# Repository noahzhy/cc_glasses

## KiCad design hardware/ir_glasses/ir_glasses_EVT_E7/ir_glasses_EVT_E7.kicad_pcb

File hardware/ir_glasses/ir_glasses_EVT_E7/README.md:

# EVT E7

**状态：静态设计验收通过，首板验证待完成。** ERC、PCB DRC 均为 0 错误、0 警告；未连接及原理图与 PCB 一致性问题均为 0。尚未进行首板实测和板厂 DFM，不能据此宣布量产放行。

唯一编辑入口：`ir_glasses_EVT_E7.kicad_pro`。

- 一张 A1 原理图：`ir_glasses_EVT_E7.kicad_sch` / `schematic.pdf`。
- 一个 PCB：`ir_glasses_EVT_E7.kicad_pcb`，已包含 carrier，无独立裸板或 carrier 工程。
- 四层、1.6 mm，所有电气元器件统一正面；光学位置、接口和机械外形沿用 E6。
- 所有过孔孔径至少 0.20 mm、外径至少 0.40 mm，单边环宽至少 0.10 mm。
- 复核及精简：`review/report.md`；验收状态：`review/validation.json`。
- 分层及装配预览：`review/pcb_layers.pdf`；采购清单：`BOM.csv`；正面贴装坐标：`assembly_positions.csv`。
- 本目录不发布制造包。E6 历史制造文件不适用于 E7。

`tools/` 为此次整改的重建和检查脚本；日常直接编辑 KiCad 工程。重建脚本会覆盖设计，不能在人工修改后直接重跑。Python 工具不引入继承类；需要 KiCad 10 的 pcbnew Python，以及 Python 3 的 sexpdata、numpy、scipy、shapely、pymupdf。

固件接口和采集协议保持 F302 版本兼容，编号 E7 不意味着更改串口协议。有效采集前等待模拟偏置稳定，首板按 `first_board_tests.csv` 验证。

量产前复核见 `review/preproduction/report.md`。工程根目录 `BOM.csv` 为逐位号明细，`BOM_采购汇总.csv` 为 39 种料号的中文采购汇总，均包含简要参数及立创商城编码；单板共 153 个装配器件。实时库存、贴片库可用性及实物验证待确认。

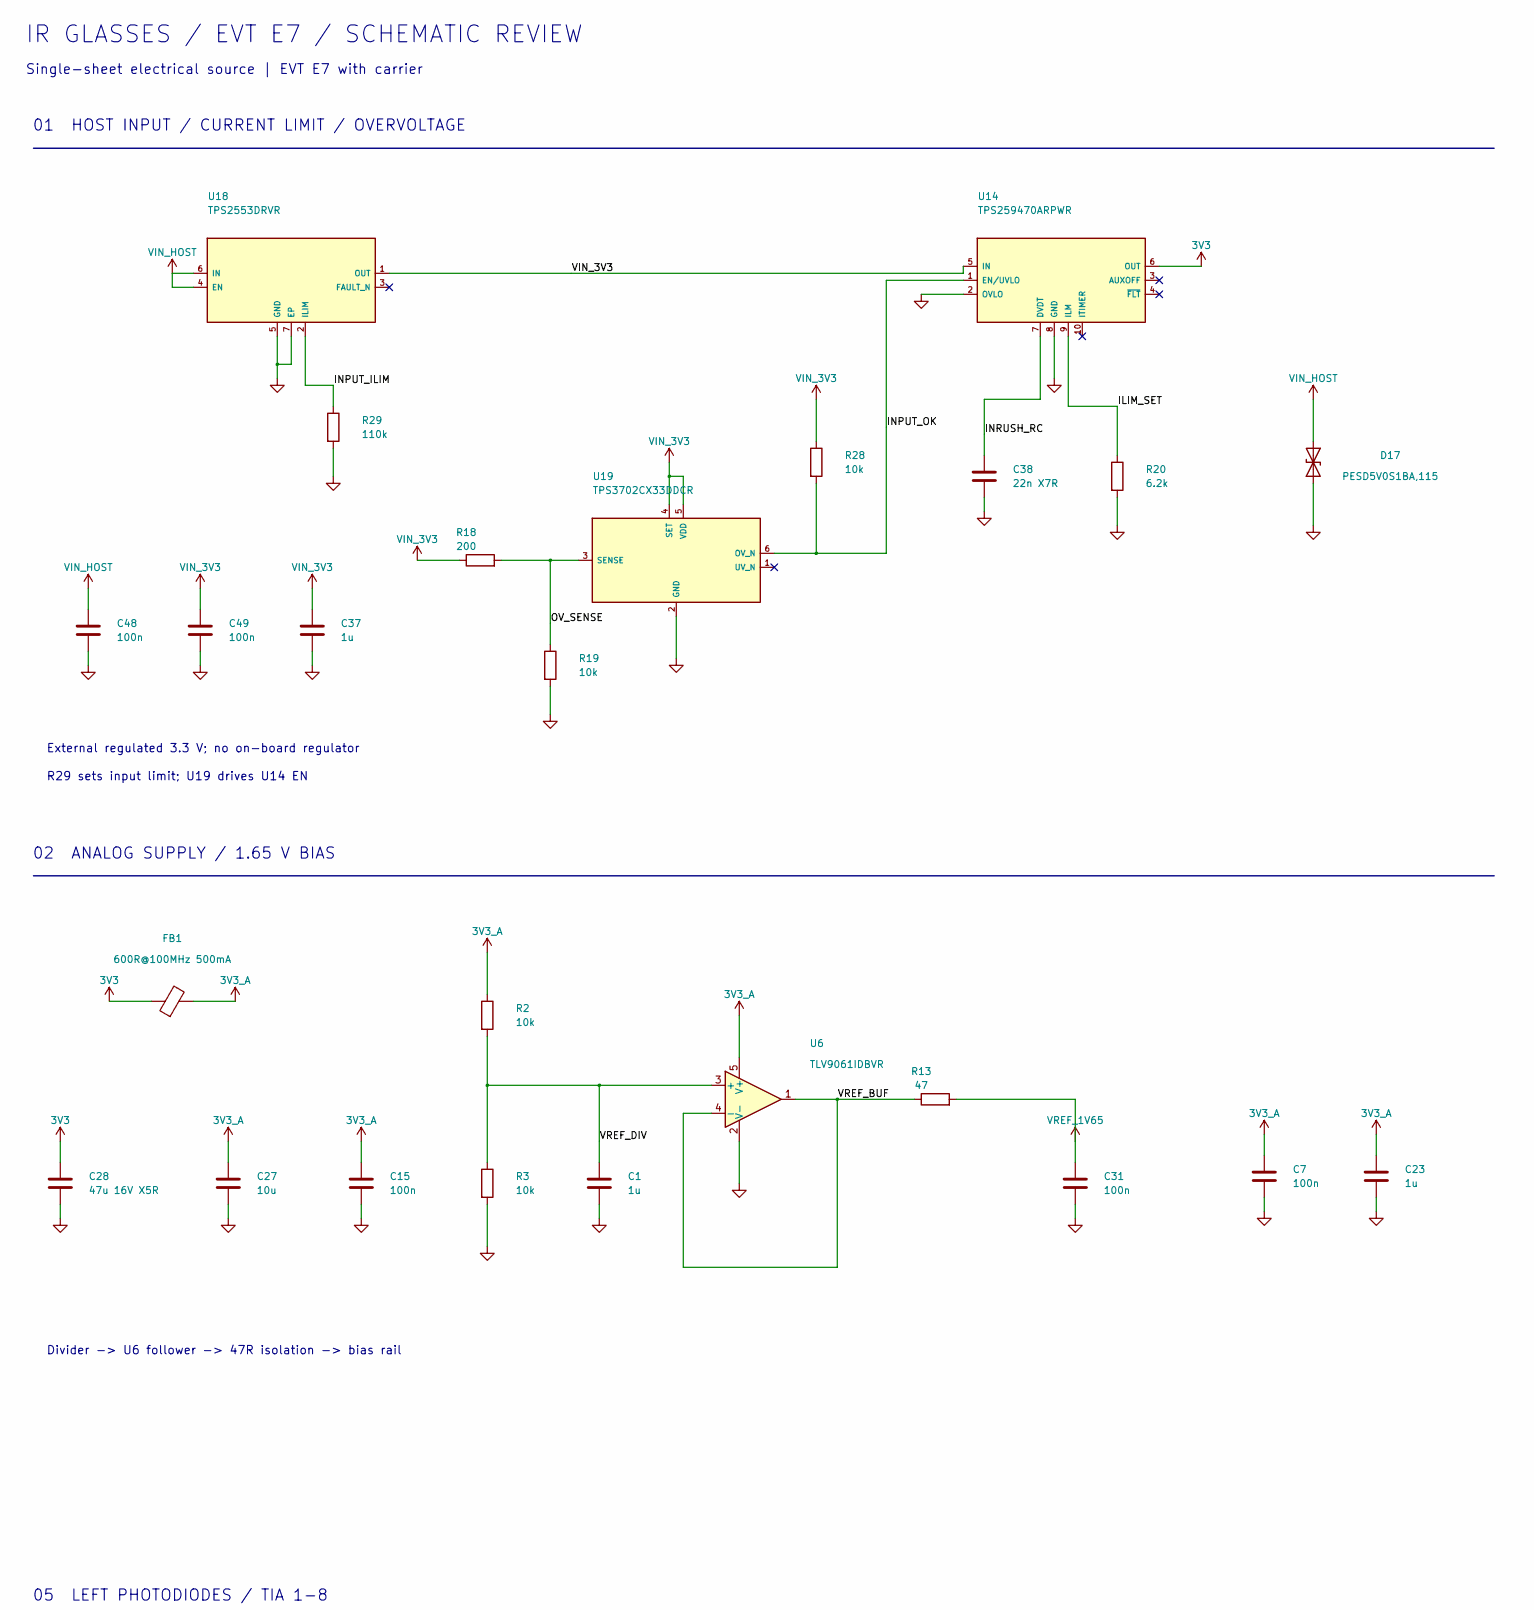
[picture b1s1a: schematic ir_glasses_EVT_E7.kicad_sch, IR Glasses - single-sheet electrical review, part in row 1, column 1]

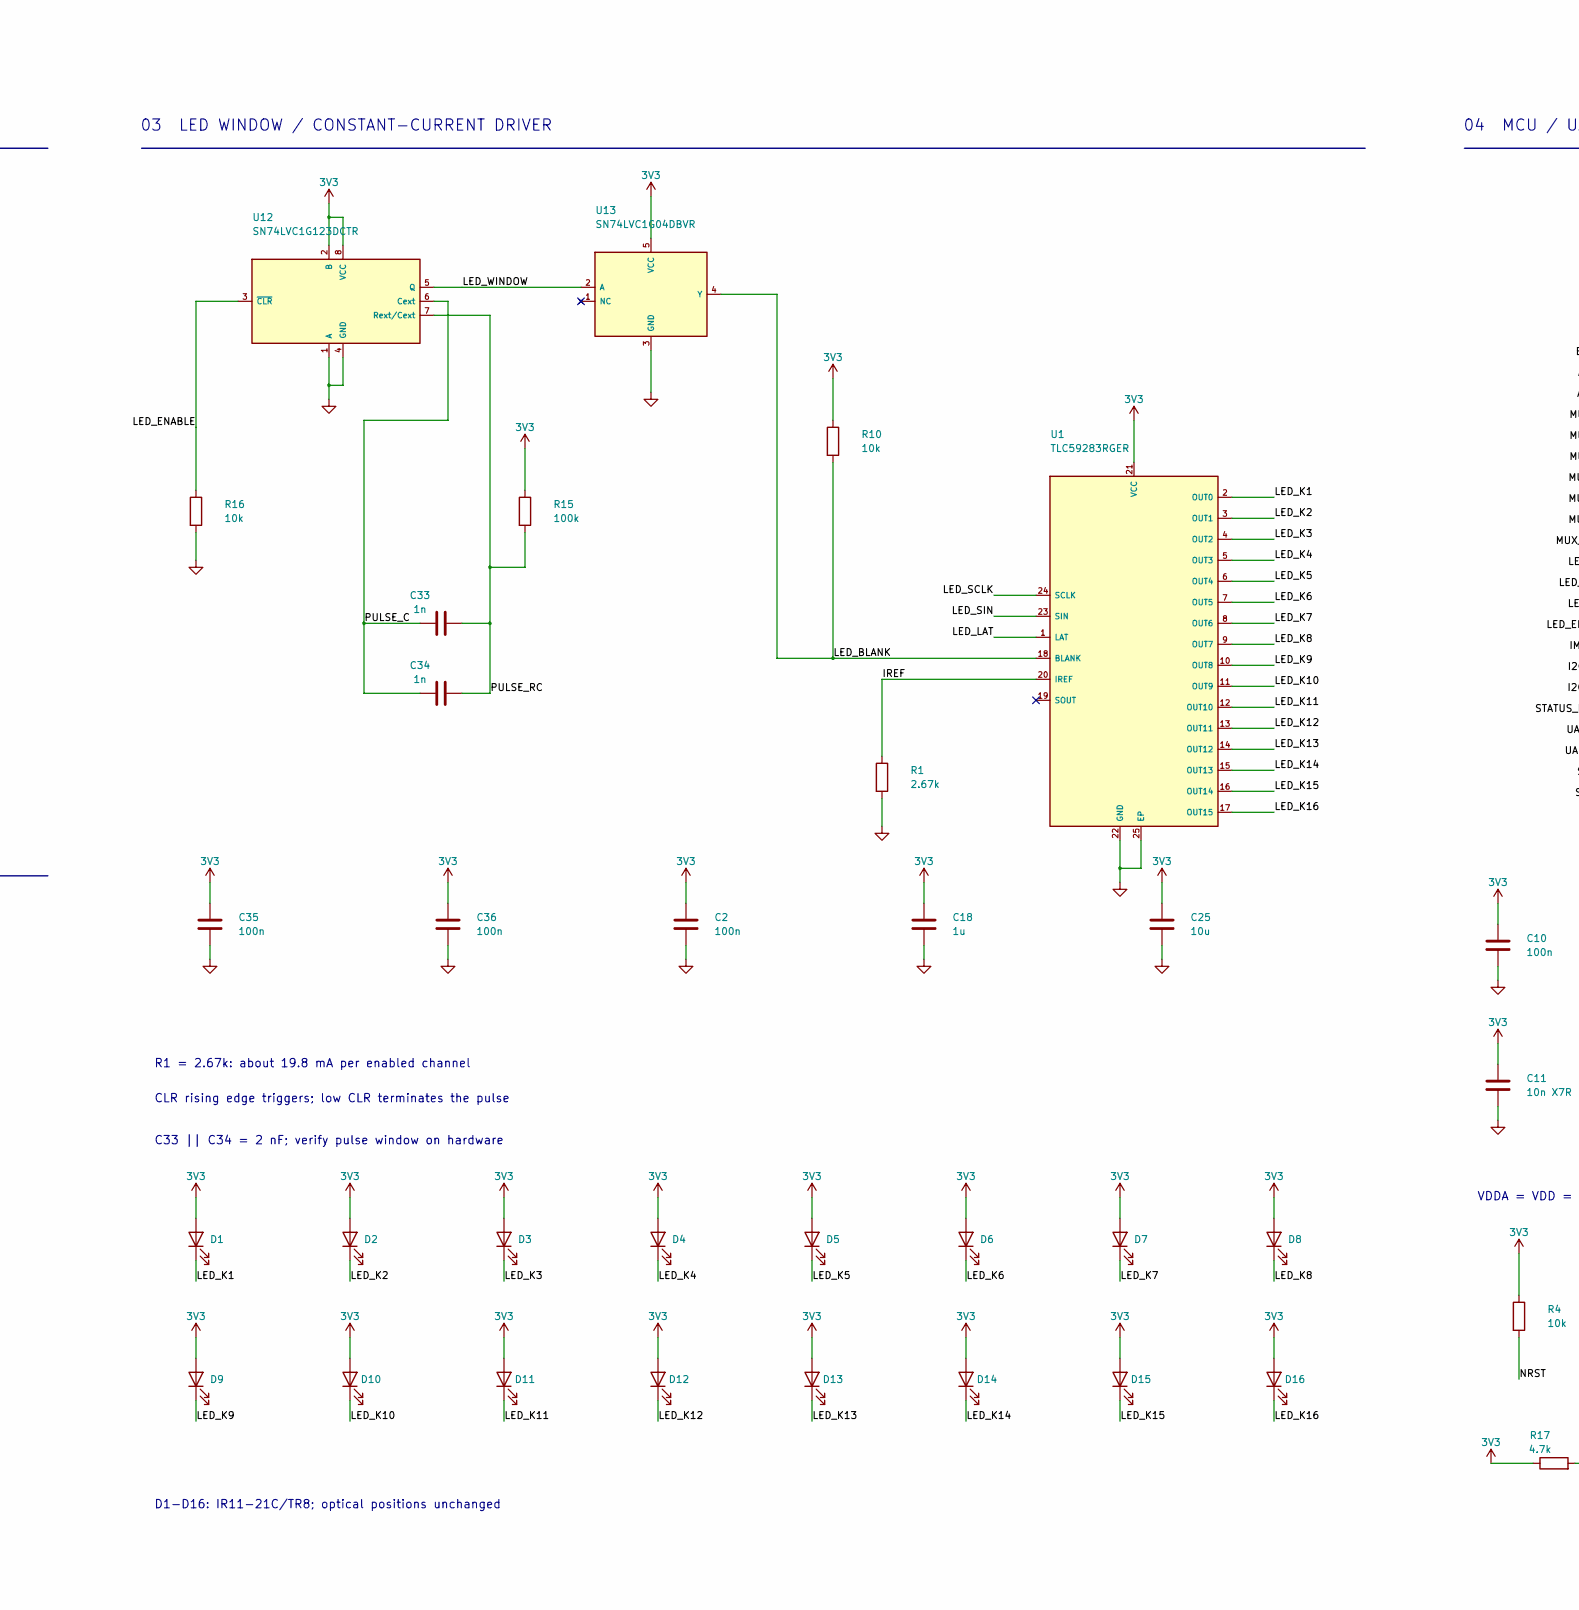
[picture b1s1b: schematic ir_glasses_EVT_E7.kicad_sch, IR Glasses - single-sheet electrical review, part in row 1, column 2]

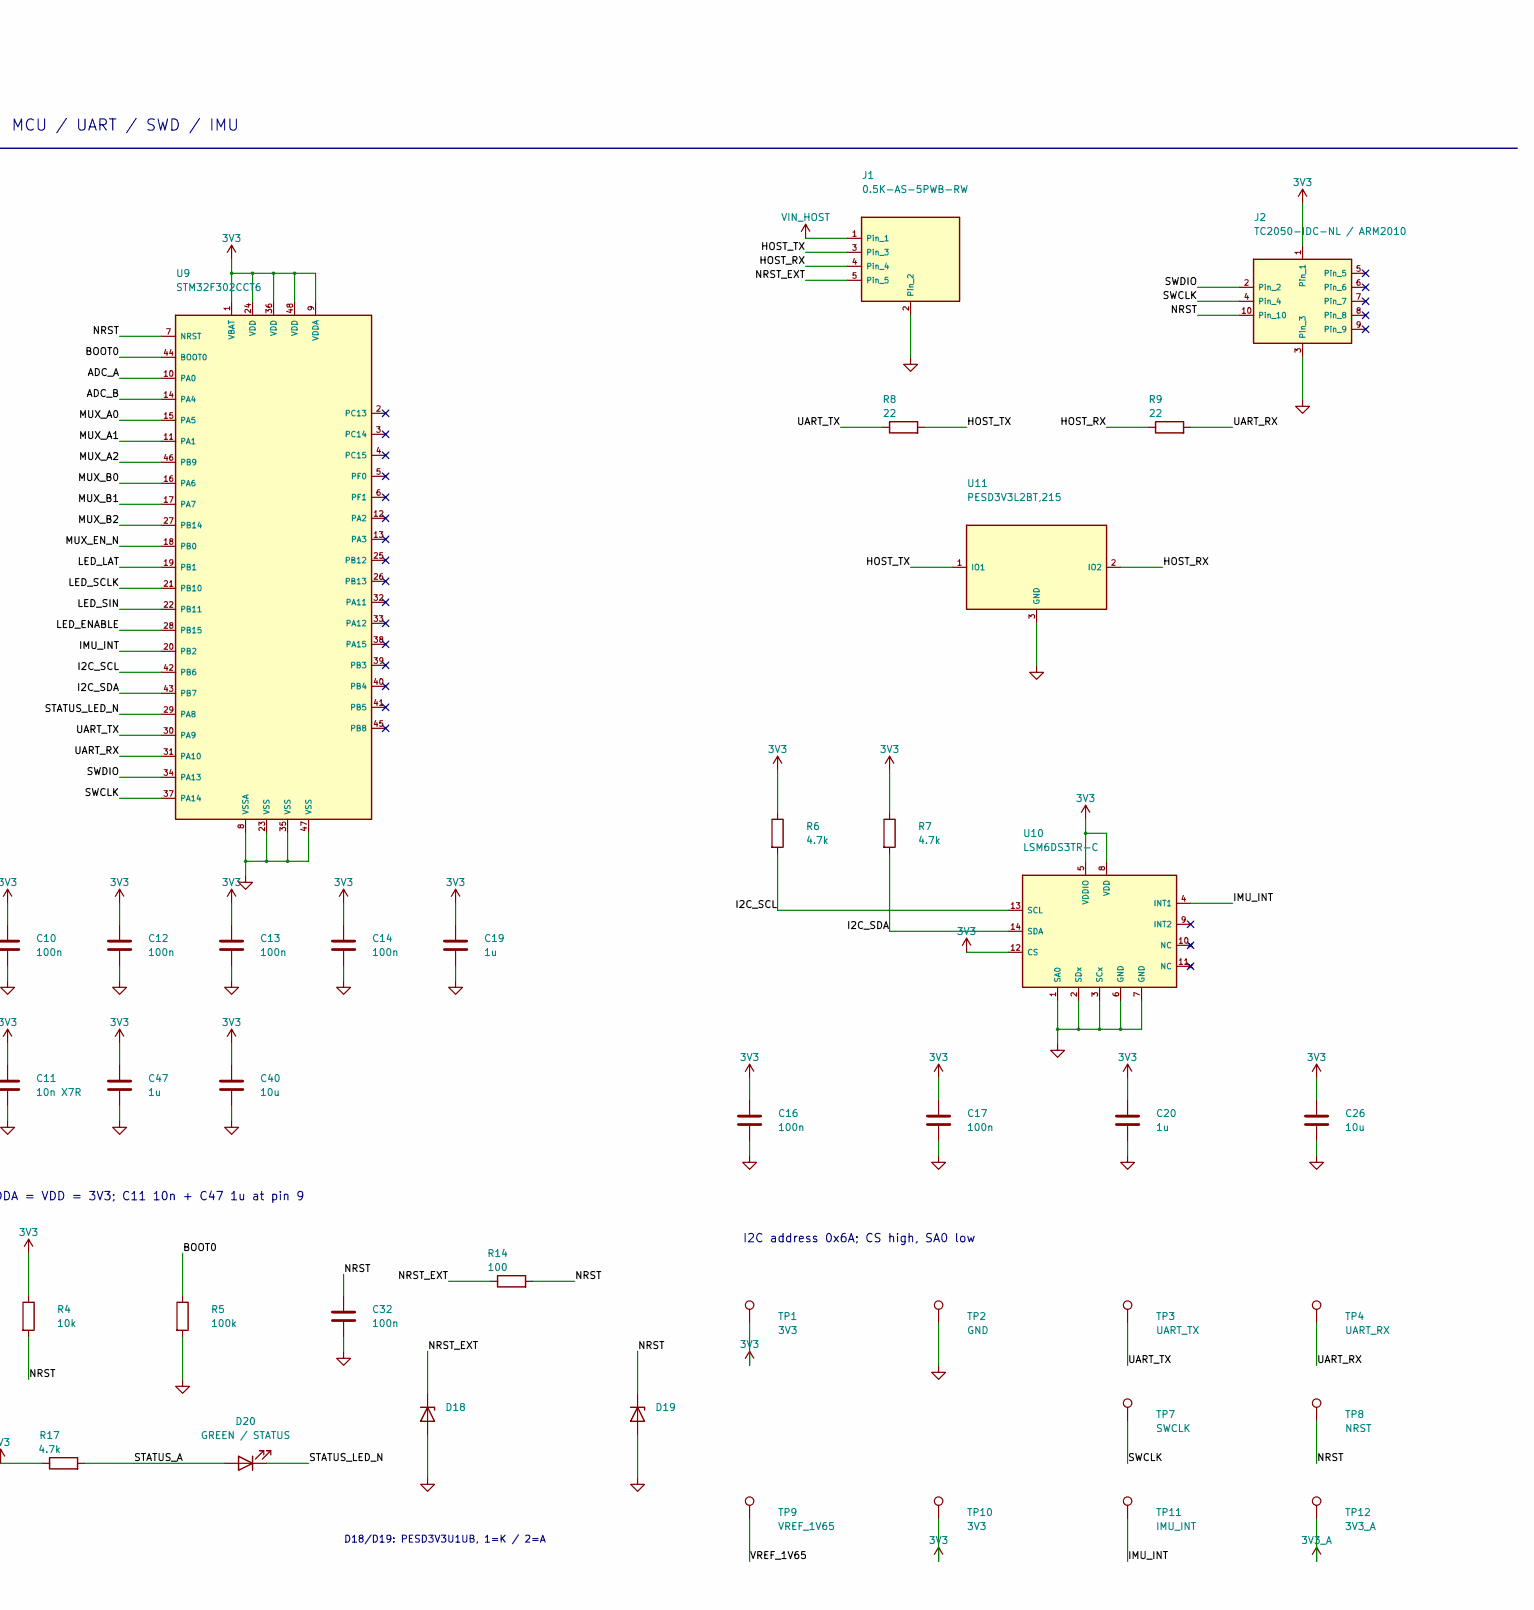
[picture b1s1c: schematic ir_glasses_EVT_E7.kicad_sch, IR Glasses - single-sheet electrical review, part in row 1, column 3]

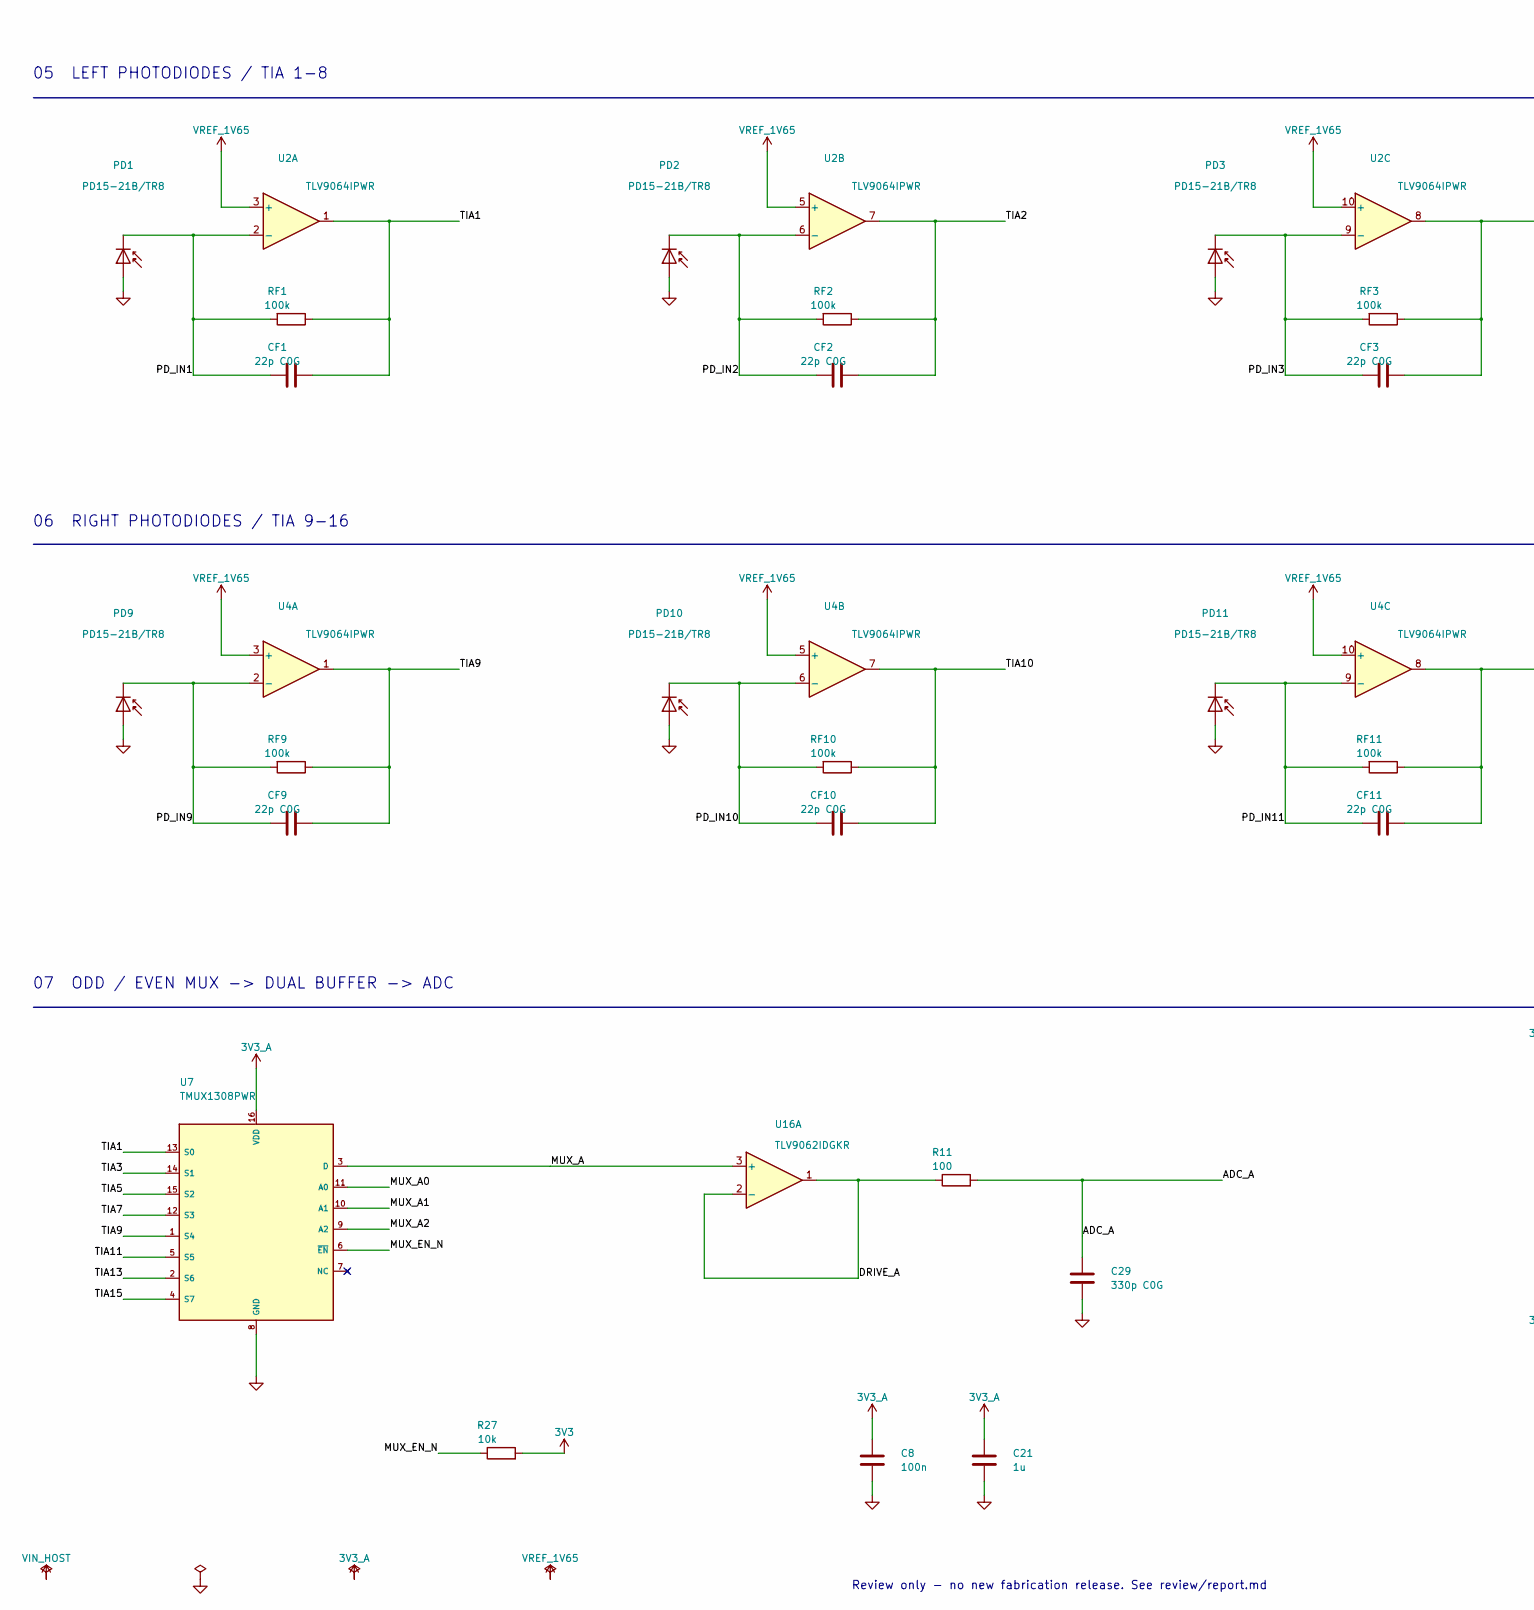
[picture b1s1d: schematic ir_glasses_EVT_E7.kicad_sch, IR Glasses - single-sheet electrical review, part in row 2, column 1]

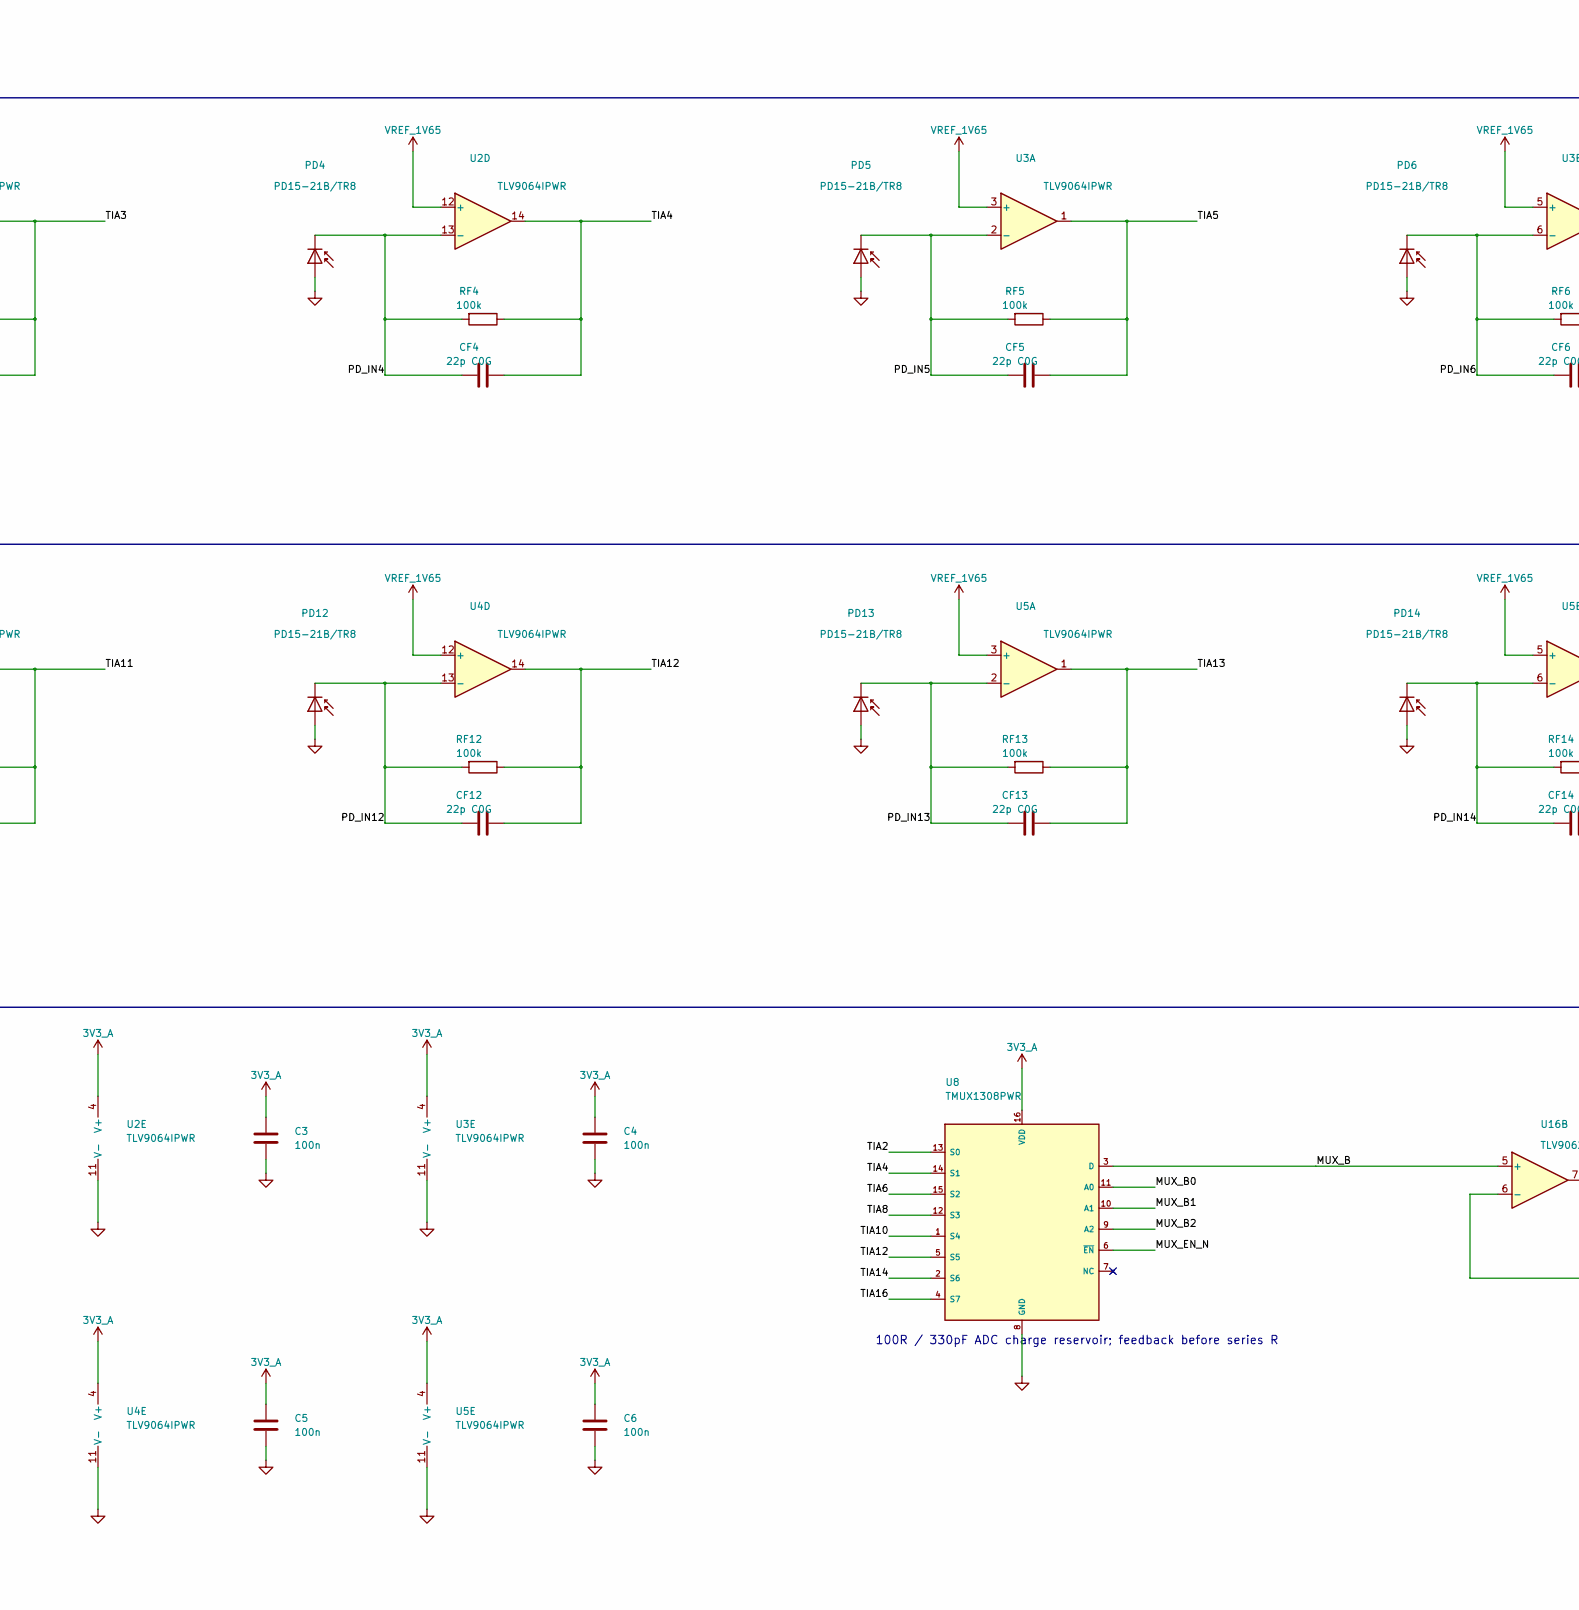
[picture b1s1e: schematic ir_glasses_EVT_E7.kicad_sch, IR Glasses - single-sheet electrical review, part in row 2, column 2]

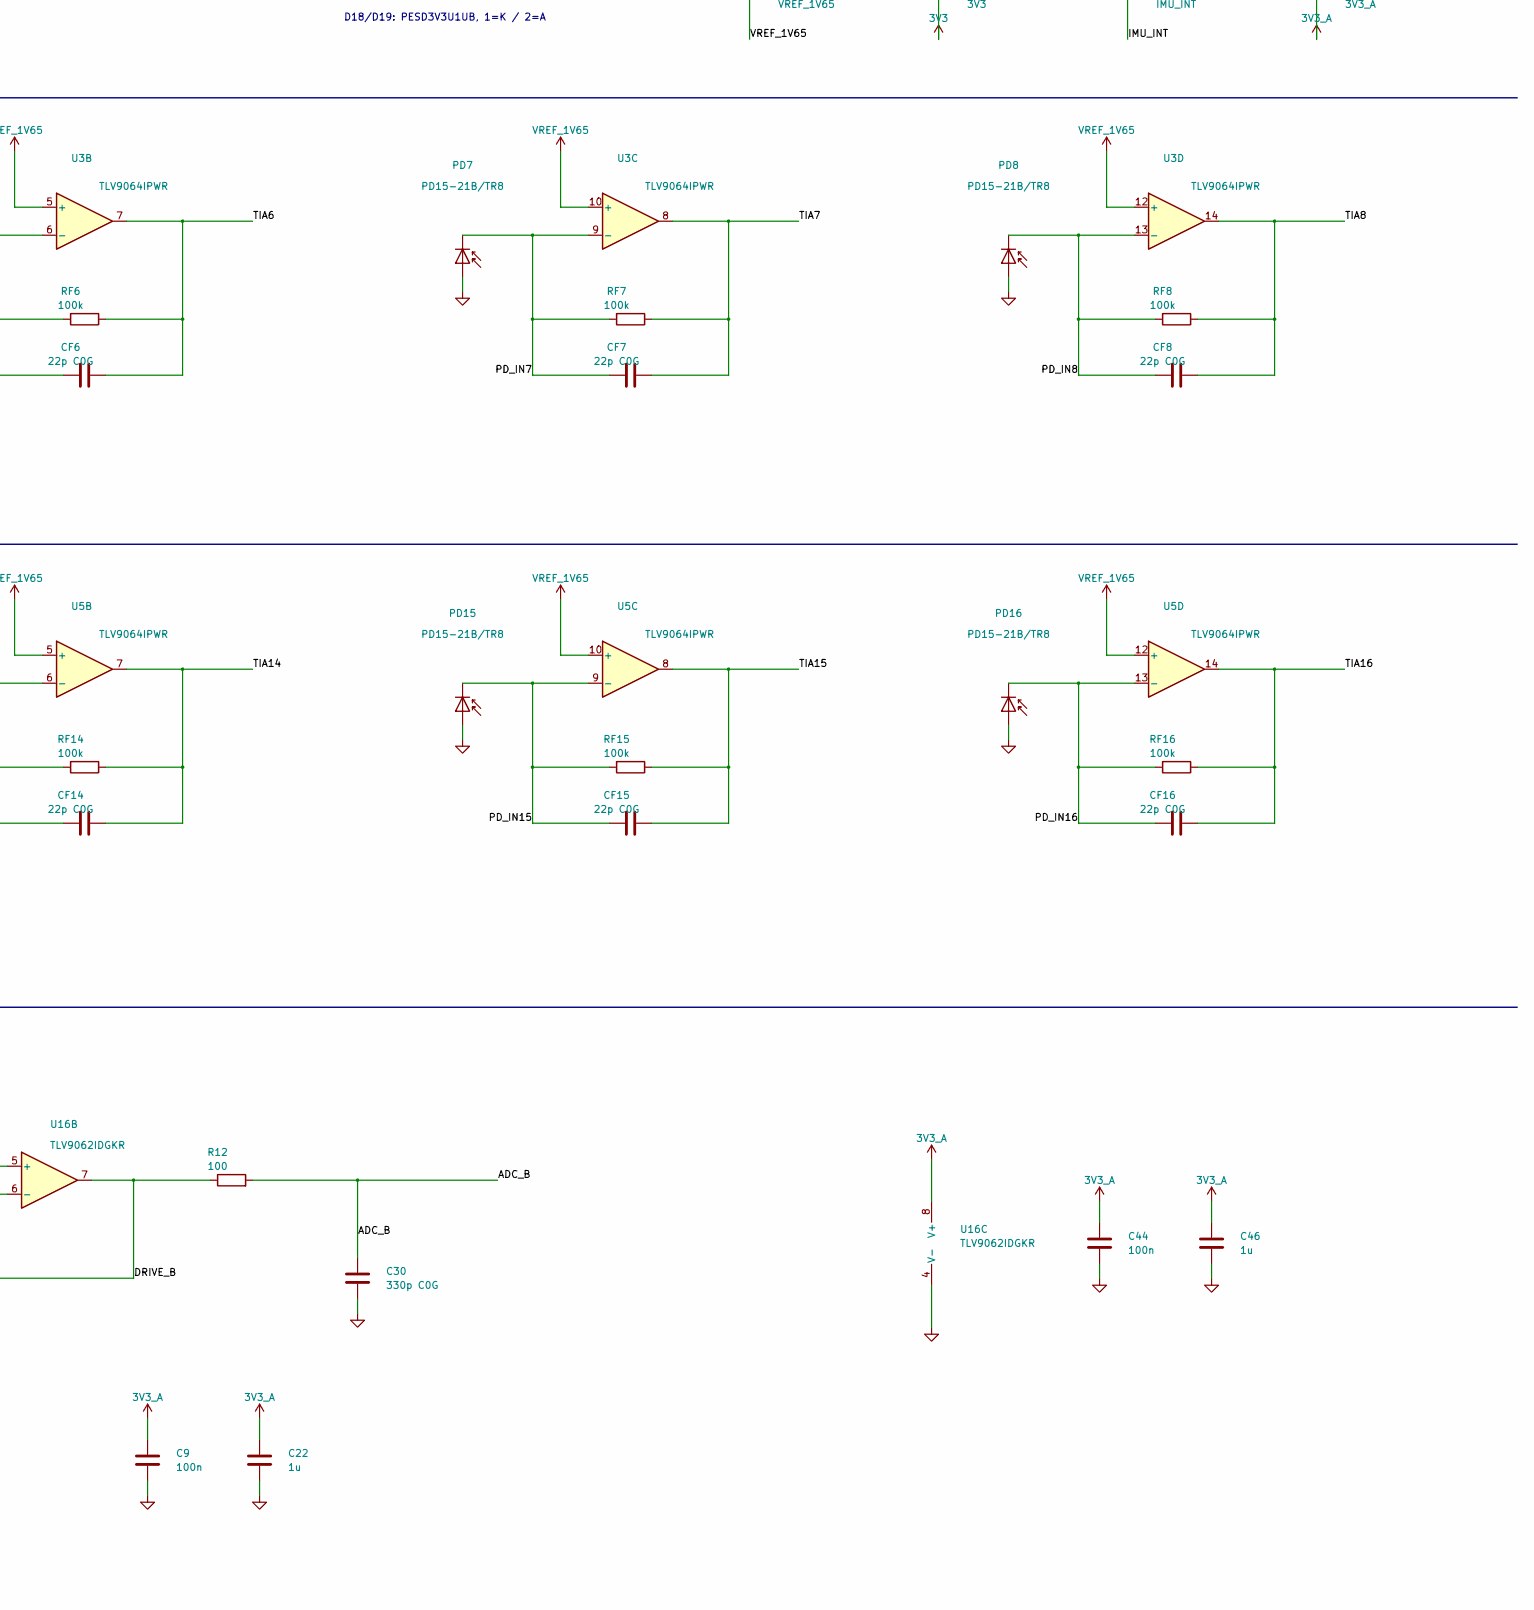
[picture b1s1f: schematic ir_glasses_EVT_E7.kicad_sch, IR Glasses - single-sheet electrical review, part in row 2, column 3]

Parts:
C1, C18, C19, C20, C21, C22, C23, C37, C46, C47: 1u; 0402; MPN TCC0402X7R105K160AT; LCSC C49210445
C2, C3, C4, C5, C6, C7, C8, C9, C10, C12, C13, C14, C15, C16, C17, C31, C32, C35, C36, C44, C48, C49: 100n; 0402; MPN CL05B104KO5NNNC; LCSC C1525
C11: 10n X7R; 0402; MPN CL05B103KB5NNNC; LCSC C15195
C25, C26, C27, C40: 10u; 0603; MPN CL10A106KP8NNNC; LCSC C19702
C28: 47u 16V X5R; 1210; MPN CC1210KKX5R7BB476; LCSC C596320
C29, C30: 330p C0G; 0402; MPN GRM1555C1H331JA01D; LCSC C76965
C33, C34: 1n; 0402; MPN 0402CG102J500NT; LCSC C53547
C38: 22n X7R; 0402; MPN CL05B223KB5VPNC; LCSC C307335
CF1, CF2, CF3, CF4, CF5, CF6, CF7, CF8, CF9, CF10, CF11, CF12, CF13, CF14, CF15, CF16: 22p C0G; 0402; MPN 0402CG220J500NT; LCSC C1555
D1, D2, D3, D4, D5, D6, D7, D8, D9, D10, D11, D12, D13, D14, D15, D16: IR11-21C/TR8; 1206; MPN IR11-21C/TR8; LCSC C19269752
D17: PESD5V0S1BA,115; SOD-323; MPN PESD5V0S1BA,115; LCSC C19224
D18, D19: PESD3V3U1UB,115; SOD-523; MPN PESD3V3U1UB,115; LCSC C2443469
D20: GREEN / STATUS; 0603; MPN LTST-C190KGKT; LCSC C125094
FB1: 600R@100MHz 500mA; 0603; MPN BLM18AG601SN1D; LCSC C19330
J1: 0.5K-AS-5PWB-RW; GUOCONN_0.5K-AS-5PWB-RW; MPN 0.5K-AS-5PWB-RW; LCSC C51901197
J2: TC2050-IDC-NL / ARM2010; TC2050
PD1, PD2, PD3, PD4, PD5, PD6, PD7, PD8, PD9, PD10, PD11, PD12, PD13, PD14, PD15, PD16: PD15-21B/TR8; 1206; MPN PD15-21B/TR8; LCSC C2921391
R1: 2.67k; 0402; MPN ARG02FTC2671; LCSC C284464
R2, R3, R4, R10, R16, R19, R27, R28: 10k; 0402; MPN 0402WGF1002TCE; LCSC C25744
R5, R15: 100k; 0402; MPN 0402WGF1003TCE; LCSC C25741
R6, R7, R17: 4.7k; 0402; MPN 0402WGF4701TCE; LCSC C25900
R8, R9: 22; 0402; MPN 0402WGF220JTCE; LCSC C25092
R11, R12, R14: 100; 0402; MPN RC0402FR-07100RL; LCSC C106232
R13: 47; 0402; MPN 0402WGF470JTCE; LCSC C25118
R18: 200; 0402; MPN 0402WGF2000TCE; LCSC C25087
R20: 6.2k; 0402; MPN 0402WGF6201TCE; LCSC C25915
R29: 110k; 0402; MPN 0402WGF1103TCE; LCSC C25745
RF1, RF2, RF3, RF4, RF5, RF6, RF7, RF8, RF9, RF10, RF11, RF12, RF13, RF14, RF15, RF16: 100k; 0402; MPN 0402WGF1003TCE; LCSC C25741
TP1, TP10: 3V3; 1mm
TP2: GND; 1mm
TP3: UART_TX; 1mm
TP4: UART_RX; 1mm
TP7: SWCLK; 1mm
TP8: NRST; 1mm
TP9: VREF_1V65; 1mm
TP11: IMU_INT; 1mm
TP12: 3V3_A; 1mm
U1: TLC59283RGER; VQFN-24; MPN TLC59283RGER; LCSC C485815
U2, U3, U4, U5: TLV9064IPWR; TSSOP-14; MPN TLV9064IPWR; LCSC C779410
U6: TLV9061IDBVR; SOT-23-5; MPN TLV9061IDBVR; LCSC C398358
U7, U8: TMUX1308PWR; TSSOP-16; MPN TMUX1308PWR; LCSC C970231
U9: STM32F302CCT6; LQFP-48; MPN STM32F302CCT6; LCSC C262946
U10: LSM6DS3TR-C; LGA-14; MPN LSM6DS3TR-C; LCSC C967633
U11: PESD3V3L2BT,215; SOT-23; MPN PESD3V3L2BT,215; LCSC C55440
U12: SN74LVC1G123DCTR; SSOP-8; MPN SN74LVC1G123DCTR; LCSC C123302
U13: SN74LVC1G04DBVR; SOT-23-5; MPN SN74LVC1G04DBVR; LCSC C7827
U14: TPS259470ARPWR; VQFN-10-HR; MPN TPS259470ARPWR; LCSC C3662799
U16: TLV9062IDGKR; VSSOP-8_3x3mm_P0.65mm; MPN TLV9062IDGKR; LCSC C398356
U18: TPS2553DRVR; TPS2553_DRV0006; MPN TPS2553DRVR; LCSC C138719
U19: TPS3702CX33DDCR; TPS3702_DDC0006; MPN TPS3702CX33DDCR; LCSC C2068031

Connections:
3V3: C2.1, C10.1, C11.1, C12.1, C13.1, C14.1, C16.1, C17.1, C18.1, C19.1, C20.1, C25.1, C26.1, C28.1, C35.1, C36.1, C40.1, C47.1, D1.1 (A), D2.1 (A), D3.1 (A), D4.1 (A), D5.1 (A), D6.1 (A), D7.1 (A), D8.1 (A), D9.1 (A), D10.1 (A), D11.1 (A), D12.1 (A), D13.1 (A), D14.1 (A), D15.1 (A), D16.1 (A), FB1.1, J2.1, R4.1, R6.1, R7.1, R10.1, R15.1, R17.1, R27.2, TP1.1, TP10.1, U1.21 (VCC), U9.1 (VBAT), U9.9 (VDDA), U9.24 (VDD), U9.36 (VDD), U9.48 (VDD), U10.5 (VDDIO), U10.8 (VDD), U10.12 (CS), U12.2 (B), U12.8 (VCC), U13.5 (VCC), U14.6 (OUT)
3V3_A: C3.1, C4.1, C5.1, C6.1, C7.1, C8.1, C9.1, C15.1, C21.1, C22.1, C23.1, C27.1, C44.1, C46.1, FB1.2, R2.1, TP12.1, U2.4 (V+), U3.4 (V+), U4.4 (V+), U5.4 (V+), U6.5 (V+), U7.16 (VDD), U8.16 (VDD), U16.8 (V+)
/ADC_A: C29.1, R11.2, U9.10 (PA0)
/ADC_B: C30.1, R12.2, U9.14 (PA4)
/BOOT0: R5.1, U9.44 (BOOT0)
/DRIVE_A: R11.1, U16.1, U16.2 (-)
/DRIVE_B: R12.1, U16.6 (-), U16.7
/HOST_RX: J1.4, R9.1, U11.2 (IO2)
/HOST_TX: J1.3, R8.2, U11.1 (IO1)
/I2C_SCL: R6.2, U9.42 (PB6), U10.13 (SCL)
/I2C_SDA: R7.2, U9.43 (PB7), U10.14 (SDA)
/ILIM_SET: R20.1, U14.9 (ILM)
/IMU_INT: TP11.1, U9.20 (PB2), U10.4 (INT1)
/INPUT_ILIM: R29.1, U18.2 (ILIM)
/INPUT_OK: R28.2, U14.1 (EN/UVLO), U19.6 (OV_N)
/INRUSH_RC: C38.1, U14.7 (DVDT)
/IREF: R1.1, U1.20 (IREF)
/LED_BLANK: R10.2, U1.18 (BLANK), U13.4 (Y)
/LED_ENABLE: R16.1, U9.28 (PB15), U12.3 (~CLR)
/LED_K1: D1.2 (K), U1.2 (OUT0)
/LED_K2: D2.2 (K), U1.3 (OUT1)
/LED_K3: D3.2 (K), U1.4 (OUT2)
/LED_K4: D4.2 (K), U1.5 (OUT3)
/LED_K5: D5.2 (K), U1.6 (OUT4)
/LED_K6: D6.2 (K), U1.7 (OUT5)
/LED_K7: D7.2 (K), U1.8 (OUT6)
/LED_K8: D8.2 (K), U1.9 (OUT7)
/LED_K9: D9.2 (K), U1.10 (OUT8)
/LED_K10: D10.2 (K), U1.11 (OUT9)
/LED_K11: D11.2 (K), U1.12 (OUT10)
/LED_K12: D12.2 (K), U1.13 (OUT11)
/LED_K13: D13.2 (K), U1.14 (OUT12)
/LED_K14: D14.2 (K), U1.15 (OUT13)
/LED_K15: D15.2 (K), U1.16 (OUT14)
/LED_K16: D16.2 (K), U1.17 (OUT15)
/LED_LAT: U1.1 (LAT), U9.19 (PB1)
/LED_SCLK: U1.24 (SCLK), U9.21 (PB10)
/LED_SIN: U1.23 (SIN), U9.22 (PB11)
/LED_WINDOW: U12.5 (Q), U13.2 (A)
/MUX_A: U7.3 (D), U16.3 (+)
/MUX_A0: U7.11 (A0), U9.15 (PA5)
/MUX_A1: U7.10 (A1), U9.11 (PA1)
/MUX_A2: U7.9 (A2), U9.46 (PB9)
/MUX_B: U8.3 (D), U16.5 (+)
/MUX_B0: U8.11 (A0), U9.16 (PA6)
/MUX_B1: U8.10 (A1), U9.17 (PA7)
/MUX_B2: U8.9 (A2), U9.27 (PB14)
/MUX_EN_N: R27.1, U7.6 (~EN), U8.6 (~EN), U9.18 (PB0)
/NRST: C32.1, D19.1 (K), J2.10, R4.2, R14.2, TP8.1, U9.7 (NRST)
/NRST_EXT: D18.1 (K), J1.5, R14.1
/OV_SENSE: R18.2, R19.1, U19.3 (SENSE)
/PD_IN1: CF1.2, PD1.2 (K), RF1.2, U2.2 (-)
/PD_IN2: CF2.2, PD2.2 (K), RF2.2, U2.6 (-)
/PD_IN3: CF3.2, PD3.2 (K), RF3.2, U2.9 (-)
/PD_IN4: CF4.2, PD4.2 (K), RF4.2, U2.13 (-)
/PD_IN5: CF5.2, PD5.2 (K), RF5.2, U3.2 (-)
/PD_IN6: CF6.2, PD6.2 (K), RF6.2, U3.6 (-)
/PD_IN7: CF7.2, PD7.2 (K), RF7.2, U3.9 (-)
/PD_IN8: CF8.2, PD8.2 (K), RF8.2, U3.13 (-)
/PD_IN9: CF9.2, PD9.2 (K), RF9.2, U4.2 (-)
/PD_IN10: CF10.2, PD10.2 (K), RF10.2, U4.6 (-)
/PD_IN11: CF11.2, PD11.2 (K), RF11.2, U4.9 (-)
/PD_IN12: CF12.2, PD12.2 (K), RF12.2, U4.13 (-)
/PD_IN13: CF13.2, PD13.2 (K), RF13.2, U5.2 (-)
/PD_IN14: CF14.2, PD14.2 (K), RF14.2, U5.6 (-)
/PD_IN15: CF15.2, PD15.2 (K), RF15.2, U5.9 (-)
/PD_IN16: CF16.2, PD16.2 (K), RF16.2, U5.13 (-)
/PULSE_C: C33.1, C34.1, U12.6 (Cext)
/PULSE_RC: C33.2, C34.2, R15.2, U12.7 (Rext/Cext)
/STATUS_A: D20.2 (A), R17.2
/STATUS_LED_N: D20.1 (K), U9.29 (PA8)
/SWCLK: J2.4, TP7.1, U9.37 (PA14)
/SWDIO: J2.2, U9.34 (PA13)
/TIA1: CF1.1, RF1.1, U2.1, U7.13 (S0)
/TIA2: CF2.1, RF2.1, U2.7, U8.13 (S0)
/TIA3: CF3.1, RF3.1, U2.8, U7.14 (S1)
/TIA4: CF4.1, RF4.1, U2.14, U8.14 (S1)
/TIA5: CF5.1, RF5.1, U3.1, U7.15 (S2)
/TIA6: CF6.1, RF6.1, U3.7, U8.15 (S2)
/TIA7: CF7.1, RF7.1, U3.8, U7.12 (S3)
/TIA8: CF8.1, RF8.1, U3.14, U8.12 (S3)
/TIA9: CF9.1, RF9.1, U4.1, U7.1 (S4)
/TIA10: CF10.1, RF10.1, U4.7, U8.1 (S4)
/TIA11: CF11.1, RF11.1, U4.8, U7.5 (S5)
/TIA12: CF12.1, RF12.1, U4.14, U8.5 (S5)
/TIA13: CF13.1, RF13.1, U5.1, U7.2 (S6)
/TIA14: CF14.1, RF14.1, U5.7, U8.2 (S6)
/TIA15: CF15.1, RF15.1, U5.8, U7.4 (S7)
/TIA16: CF16.1, RF16.1, U5.14, U8.4 (S7)
/UART_RX: R9.2, TP4.1, U9.31 (PA10)
/UART_TX: R8.1, TP3.1, U9.30 (PA9)
/VREF_BUF: R13.1, U6.1, U6.4 (-)
/VREF_DIV: C1.1, R2.2, R3.1, U6.3 (+)
GND: C1.2, C2.2, C3.2, C4.2, C5.2, C6.2, C7.2, C8.2, C9.2, C10.2, C11.2, C12.2, C13.2, C14.2, C15.2, C16.2, C17.2, C18.2, C19.2, C20.2, C21.2, C22.2, C23.2, C25.2, C26.2, C27.2, C28.2, C29.2, C30.2, C31.2, C32.2, C35.2, C36.2, C37.2, C38.2, C40.2, C44.2, C46.2, C47.2, C48.2, C49.2, D17.2 (A2), D18.2 (A), D19.2 (A), J1.2, J2.3, PD1.1 (A), PD2.1 (A), PD3.1 (A), PD4.1 (A), PD5.1 (A), PD6.1 (A), PD7.1 (A), PD8.1 (A), PD9.1 (A), PD10.1 (A), PD11.1 (A), PD12.1 (A), PD13.1 (A), PD14.1 (A), PD15.1 (A), PD16.1 (A), R1.2, R3.2, R5.2, R16.2, R19.2, R20.2, R29.2, TP2.1, U1.22 (GND), U1.25 (EP), U2.11 (V-), U3.11 (V-), U4.11 (V-), U5.11 (V-), U6.2 (V-), U7.8 (GND), U8.8 (GND), U9.8 (VSSA), U9.23 (VSS), U9.35 (VSS), U9.47 (VSS), U10.1 (SA0), U10.2 (SDx), U10.3 (SCx), U10.6 (GND), U10.7 (GND), U11.3 (GND), U12.1 (A), U12.4 (GND), U13.3 (GND), U14.2 (OVLO), U14.8 (GND), U16.4 (V-), U18.5 (GND), U18.7 (EP), U19.2 (GND)
VIN_3V3: C37.1, C49.1, R18.1, R28.1, U14.5 (IN), U18.1 (OUT), U19.4 (SET), U19.5 (VDD)
VIN_HOST: C48.1, D17.1 (A1), J1.1, U18.4 (EN), U18.6 (IN)
VREF_1V65: C31.1, R13.2, TP9.1, U2.3 (+), U2.5 (+), U2.10 (+), U2.12 (+), U3.3 (+), U3.5 (+), U3.10 (+), U3.12 (+), U4.3 (+), U4.5 (+), U4.10 (+), U4.12 (+), U5.3 (+), U5.5 (+), U5.10 (+), U5.12 (+)

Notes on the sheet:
IR GLASSES / EVT E7 / SCHEMATIC REVIEW
Single-sheet electrical source | EVT E7 with carrier
01 HOST INPUT / CURRENT LIMIT / OVERVOLTAGE
External regulated 3.3 V; no on-board regulator
R29 sets input limit; U19 drives U14 EN
02 ANALOG SUPPLY / 1.65 V BIAS
Divider -> U6 follower -> 47R isolation -> bias rail
03 LED WINDOW / CONSTANT-CURRENT DRIVER
R1 = 2.67k: about 19.8 mA per enabled channel
CLR rising edge triggers; low CLR terminates the pulse
C33 || C34 = 2 nF; verify pulse window on hardware
D1-D16: IR11-21C/TR8; optical positions unchanged
04 MCU / UART / SWD / IMU
VDDA = VDD = 3V3; C11 10n + C47 1u at pin 9
D18/D19: PESD3V3U1UB, 1=K / 2=A
I2C address 0x6A; CS high, SA0 low
05 LEFT PHOTODIODES / TIA 1-8
06 RIGHT PHOTODIODES / TIA 9-16
07 ODD / EVEN MUX -> DUAL BUFFER -> ADC
100R / 330pF ADC charge reservoir; feedback before series R
Review only - no new fabrication release. See review/report.md
